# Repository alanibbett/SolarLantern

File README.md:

# SolarLantern
Solar lantern based on QX5252 Joule Thief. 

Thanks to Nitesh Kadyan at 
https://hackaday.io/project/120823-solar-lantern-soldering-kit for the idea.

Parts list is included in the repo.

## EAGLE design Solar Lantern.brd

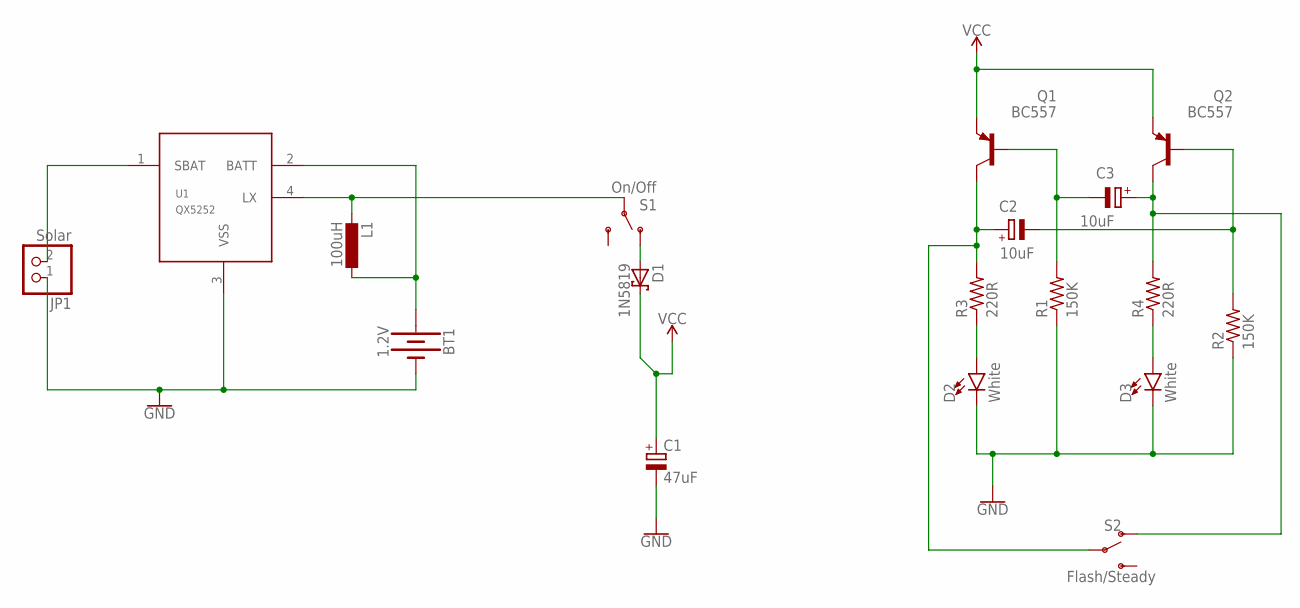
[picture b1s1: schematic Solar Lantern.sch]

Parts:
BT1: 1.2V; BATTERY-AA
C1: 47uF; E3,5-8
C2, C3: 10uF; E2,5-7
D1: 1N5819; DO35-7
D2, D3: White; LED_5MM
JP1: Solar; 1X02
L1: 100uH; 0207/10
Q1, Q2: BC557; TO92
R1, R2: 150K; 0207/10
R3, R4: 220R; 0207/10
S1: On/Off; SWITCH_SPDT_PTH_11.6X4.0MM
S2: Flash/Steady; SWITCH_SPDT_PTH_11.6X4.0MM
U1: QX5252; TO94

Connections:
GND: BT1.GND@1 (-), C1.-, D2.K (C), D3.K (C), JP1.1, R1.1, R2.1, U1.3 (VSS)
unnamed: C3.-, Q1.2 (B), R1.2
unnamed: C2.-, Q2.2 (B), R2.2
unnamed: C3.+, Q2.3 (C), R4.2, S2.1 (O)
unnamed: D3.A, R4.1
unnamed: C2.+, Q1.3 (C), R3.2, S2.2
unnamed: D2.A, R3.1
unnamed: JP1.2, U1.1 (SBAT)
unnamed: L1.2, S1.2, U1.4 (LX)
unnamed: BT1.PWR@1 (+), L1.1, U1.2 (BATT)
unnamed: D1.A, S1.1 (O)
VCC: C1.+, D1.C, Q1.1 (E), Q2.1 (E)

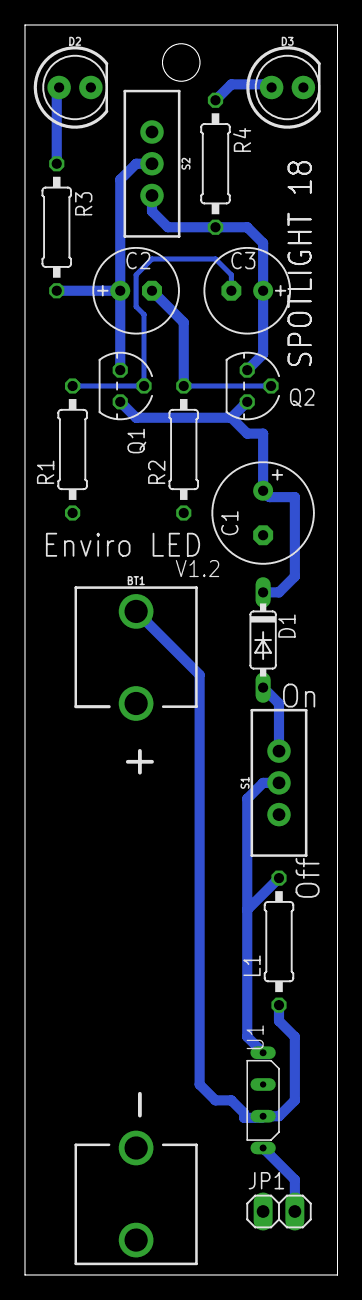
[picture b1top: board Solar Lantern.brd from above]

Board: 2 copper layers, 25.0 x 100.0 mm, 18 parts (0 on the bottom side), 12 nets.

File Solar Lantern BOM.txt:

Partlist exported from /Users/aibbett/Dropbox/Engineering/ALICAD eagle/Solar Lantern/Solar Lantern.sch at 1/7/18 2:06 PM

Part Value        Device                     Package                    Description                             PROD_ID    SF_SKU    SPICEPREFIX
BT1  1.2V         BATTERY-AA                 BATTERY-AA                 Battery - Single Cell                   BATT-08316 PRT-07949            
C1   47uF         CPOL-EUE3.5-8              E3,5-8                     POLARIZED CAPACITOR, European symbol                         C          
C2   10uF         CPOL-EUE2.5-7              E2,5-7                     POLARIZED CAPACITOR, European symbol                         C          
C3   10uF         CPOL-EUE2.5-7              E2,5-7                     POLARIZED CAPACITOR, European symbol                         C          
D1   1N5819       SCHOTTKY-DIODEDO35-7       DO35-7                     Schottky Diode                                                          
D2   White        LED5MM                     LED_5MM                    LED (Generic)                                                           
D3   White        LED5MM                     LED_5MM                    LED (Generic)                                                           
JP1  Solar        PINHD-1X2                  1X02                       PIN HEADER                                                              
L1   100uH        L-EU0207/10                0207/10                    INDUCTOR, European symbol                                               
Q1   BC557        BC557                      TO92                       PNP Transistor                                                          
Q2   BC557        BC557                      TO92                       PNP Transistor                                                          
R1   150K         R-US_0207/10               0207/10                    RESISTOR, American symbol                                    R          
R2   150K         R-US_0207/10               0207/10                    RESISTOR, American symbol                                    R          
R3   220R         R-US_0207/10               0207/10                    RESISTOR, American symbol                                    R          
R4   220R         R-US_0207/10               0207/10                    RESISTOR, American symbol                                    R          
S1   On/Off       SWITCH-SPDT-PTH-11.6X4.0MM SWITCH_SPDT_PTH_11.6X4.0MM Single Pole, Double Throw (SPDT) Switch SWCH-08261 COM-00102            
S2   Flash/Steady SWITCH-SPDT-PTH-11.6X4.0MM SWITCH_SPDT_PTH_11.6X4.0MM Single Pole, Double Throw (SPDT) Switch SWCH-08261 COM-00102            
U1   QX5252       QX5252                     TO94                       QX5252

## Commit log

2018-07-01 Add files via upload
    Initial upload
2018-07-01 Add files via upload
    Bill of materials
2018-07-01 Rename Solar Lantern.txt to Solar Lantern BOM.txt
2018-07-01 Add files via upload
    Circuit Diagram in PDF
2018-07-01 Add files via upload
    Parts layout in pdf
2018-07-01 Add files via upload
    Parts layout for solar lantern project
2018-07-13 Library Update
    changed the package for the QX5252 to make it easier to solder.

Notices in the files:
parts and their libraries:
SparkFun-Batteries: Licensing: Creative Commons ShareAlike 4.0 International - https://creativecommons.org/licenses/by-sa/4.0
